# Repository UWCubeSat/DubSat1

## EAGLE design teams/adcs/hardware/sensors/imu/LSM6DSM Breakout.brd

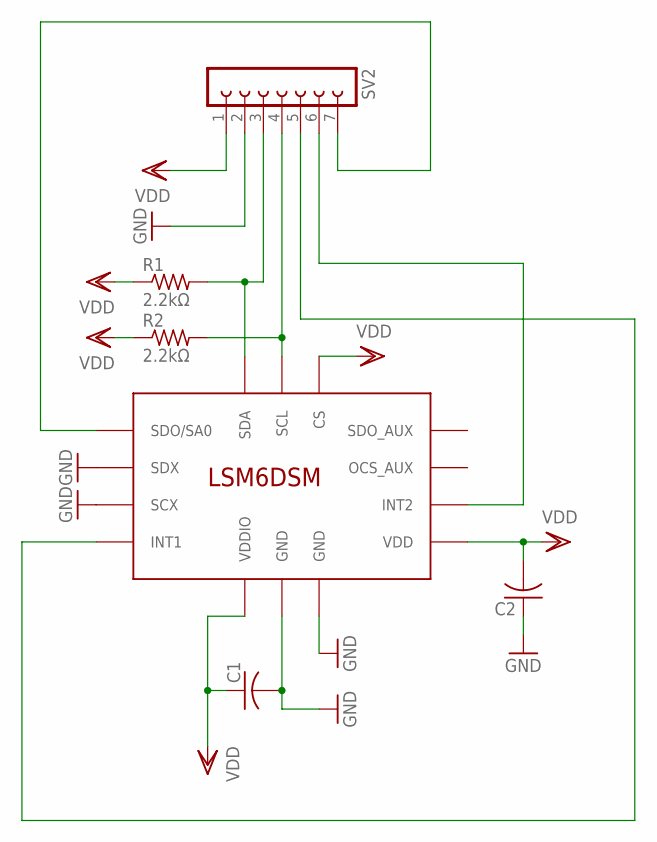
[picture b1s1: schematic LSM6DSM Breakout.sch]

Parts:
C1, C2: C-USC0805; C0805
R1, R2: 2.2kΩ; M0805
SV2: FE07-1; FE07
U$1: LSM6DSM

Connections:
GND: C1.2, C2.1, SV2.2, U$1.GND@1 (GND), U$1.GND@2 (GND), U$1.SCX, U$1.SDX
unnamed: SV2.5, U$1.INT1
unnamed: R1.2, SV2.3, U$1.SDA
unnamed: R2.2, SV2.4, U$1.SCL
unnamed: SV2.6, U$1.INT2
unnamed: SV2.7, U$1.SDO/SA0
VDD: C1.1, C2.2, R1.1, R2.1, SV2.1, U$1.CS, U$1.VDD, U$1.VDDIO

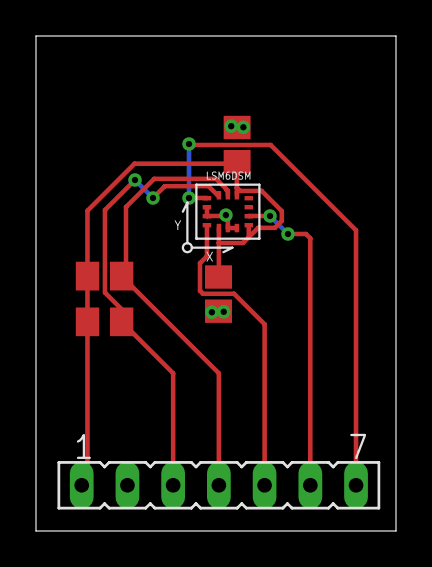
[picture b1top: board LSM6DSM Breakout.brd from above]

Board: 2 copper layers, 20.0 x 27.5 mm, 6 parts (0 on the bottom side), 7 nets.

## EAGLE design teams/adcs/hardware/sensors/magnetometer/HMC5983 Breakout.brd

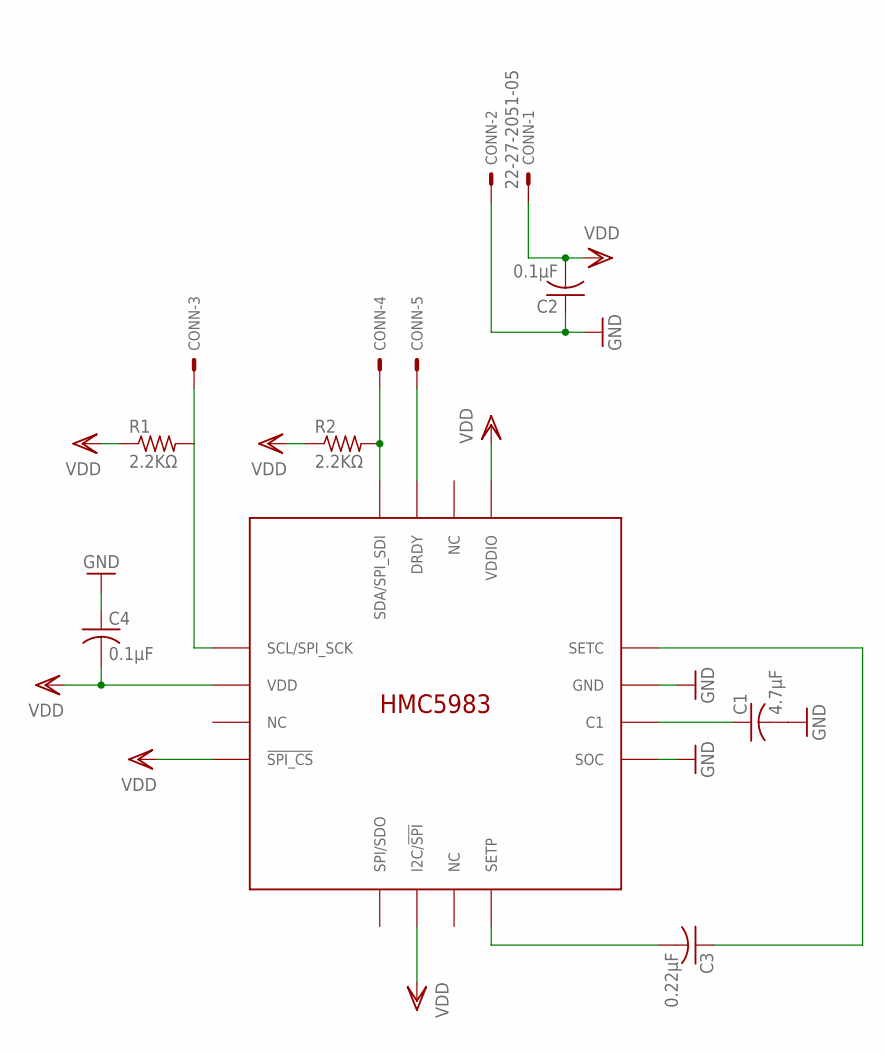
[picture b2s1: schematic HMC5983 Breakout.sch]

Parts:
C1: 4.7µF; C0805
C2: 0.1µF; C0805
C3: 0.22µF; C0805
C4: 0.1μF; C0805
CONN: 22-27-2051-05; 6410-05
R1, R2: 2.2KΩ; R0805
U$1: HMC5983

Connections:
GND: C1.2, C2.1, C4.1, CONN.2, U$1.GND, U$1.SOC
unnamed: CONN.4, R2.2, U$1.SDA/SPI_SDI
unnamed: CONN.3, R1.2, U$1.SCL/SPI_SCK
unnamed: CONN.5, U$1.DRDY
unnamed: C1.1, U$1.C1
unnamed: C3.2, U$1.SETP
unnamed: C3.1, U$1.SETC
VDD: C2.2, C4.2, CONN.1, R1.1, R2.1, U$1.!SPI_CS, U$1.I2C/!SPI, U$1.VDD, U$1.VDDIO

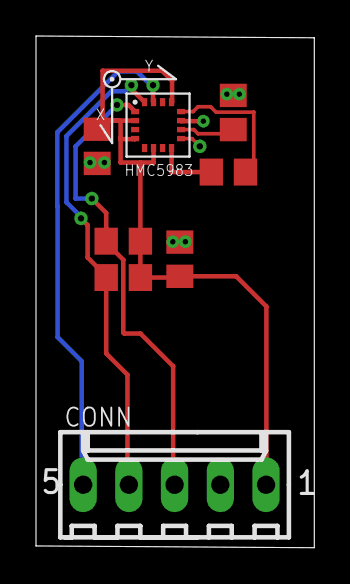
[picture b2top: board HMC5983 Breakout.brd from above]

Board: 2 copper layers, 15.5 x 28.4 mm, 8 parts (0 on the bottom side), 8 nets.

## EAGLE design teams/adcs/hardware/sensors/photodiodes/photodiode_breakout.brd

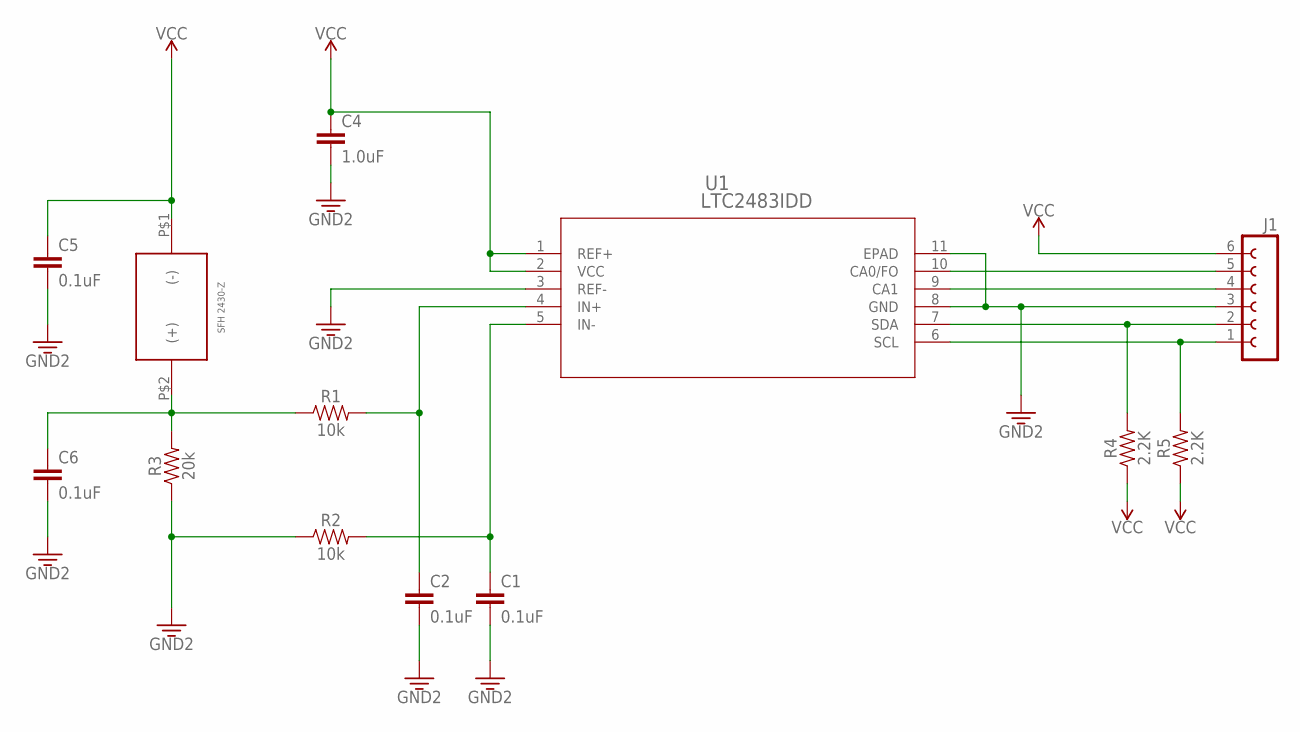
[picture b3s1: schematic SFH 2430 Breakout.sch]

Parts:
C1, C2, C5, C6: 0.1uF; 0603
C4: 1.0uF; 0805
J1: FE06-1; FE06
R1, R2: 10k; 0805
R3: 20k; 0805
R4, R5: 2.2K; 0805
U1: LTC2483IDD; DFN-10_DD
U$1: SFH-2430-Z; DIL

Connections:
GND: C1.2, C2.2, C4.2, C5.2, C6.2, J1.3, R2.1, R3.1, U1.3 (REF-), U1.8 (GND), U1.11 (EPAD)
unnamed: J1.1, R5.2, U1.6 (SCL)
unnamed: C1.1, R2.2, U1.5 (IN-)
unnamed: C2.1, R1.2, U1.4 (IN+)
unnamed: J1.2, R4.2, U1.7 (SDA)
unnamed: J1.4, U1.9 (CA1)
unnamed: J1.5, U1.10 (CA0/FO)
unnamed: C6.1, R1.1, R3.2, U$1.P$2 ((+))
VCC: C4.1, C5.1, J1.6, R4.1, R5.1, U1.1 (REF+), U1.2 (VCC), U$1.P$1 ((-))

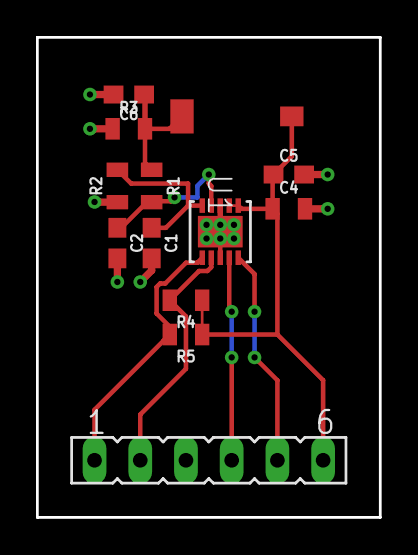
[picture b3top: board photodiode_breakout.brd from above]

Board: 2 copper layers, 19.1 x 26.7 mm, 13 parts (0 on the bottom side), 9 nets.

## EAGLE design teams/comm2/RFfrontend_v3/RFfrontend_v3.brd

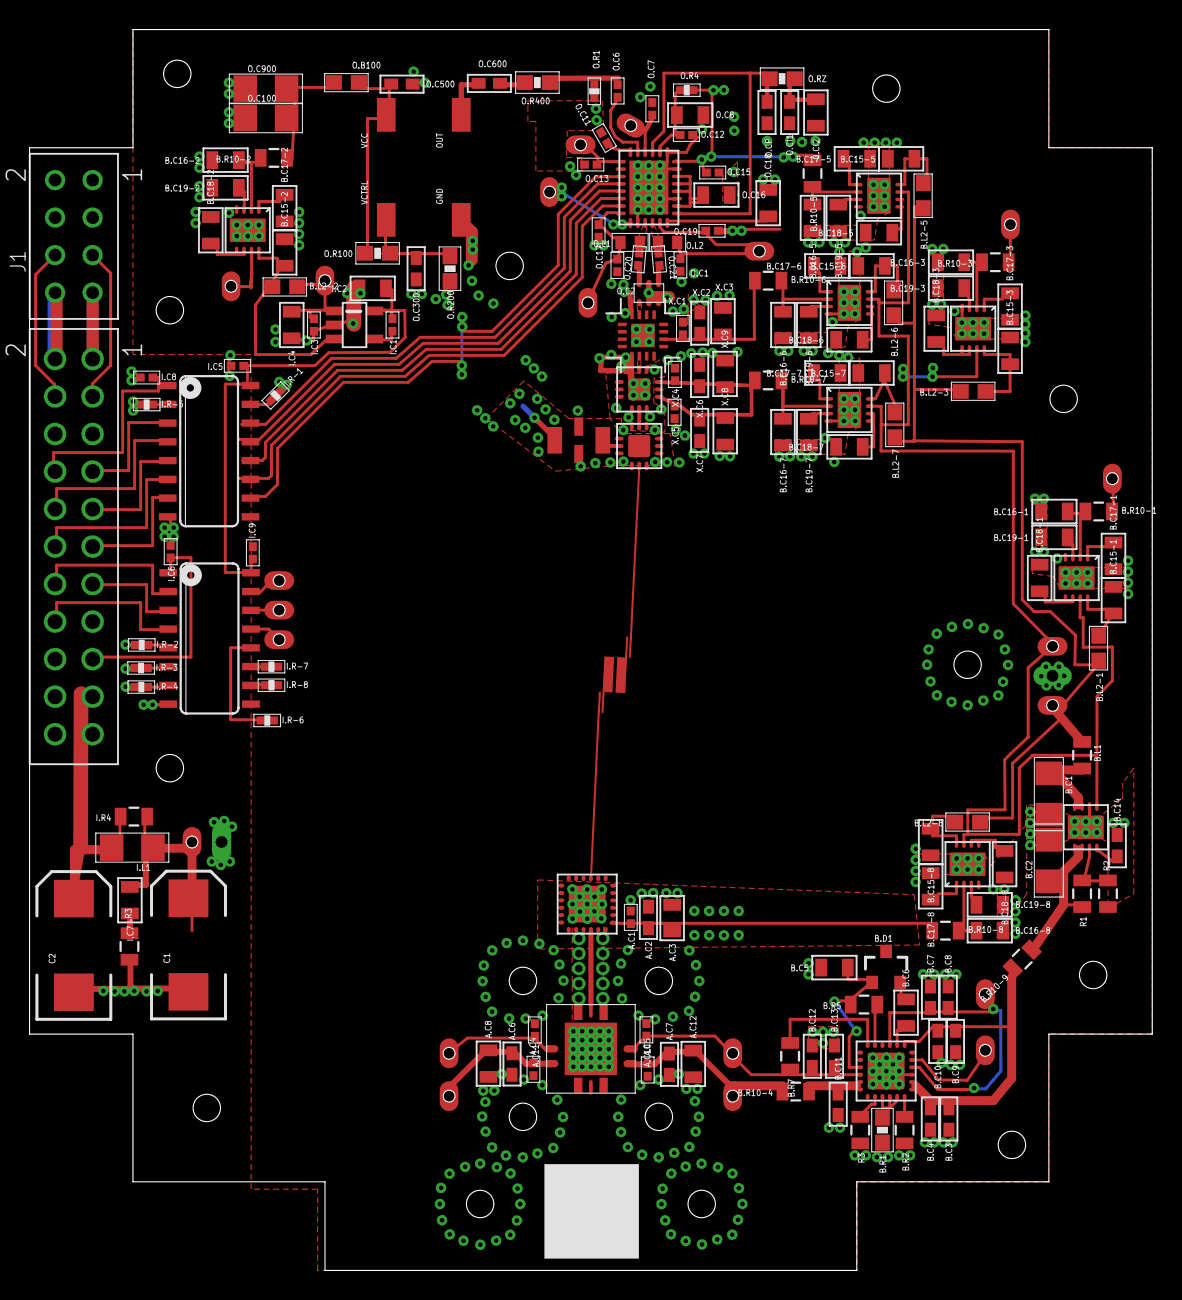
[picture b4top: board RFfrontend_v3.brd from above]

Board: 3 copper layers, 76.0 x 84.0 mm, 213 parts (1 on the bottom side), 117 nets.

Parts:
0.CI2: 0805
3.3V: 1PIN_B-T-B_TOPPAD
A.C1, A.C4, A.C5, A.C10, A.C11: 0402-CAP
A.C2, A.C6, A.C7: 0603-CAP
A.C3, A.C8, A.C12: 0805
B.C1, B.C2: 4.7u; 1206
B.C3, B.C8, B.C9, B.C12: 4.7u; 0603-CAP
B.C4, B.C7, B.C10, B.C11, B.C13, B.C14: 10n; 0603-CAP
B.C5, B.C15-1, B.C15-2, B.C15-3, B.C15-5, B.C15-6, B.C15-7, B.C15-8, B.C16-1, B.C16-2, B.C16-3, B.C16-5, B.C16-6, B.C16-7, B.C16-8, B.C17-1, B.C17-2, B.C17-3, B.C17-5, B.C17-6, B.C17-7, B.C17-8: 10u; 0805
B.C6, B.C18-1, B.C18-2, B.C18-3, B.C18-5, B.C18-6, B.C18-7, B.C18-8, B.C19-1, B.C19-2, B.C19-3, B.C19-5, B.C19-6, B.C19-7, B.C19-8: 1u; 0805
B.D1: ONSEMI_DIODE_BAT54SL; SOT23-3
B.L1, B.R10-1, B.R10-2, B.R10-3, B.R10-4, B.R10-5, B.R10-6, B.R10-7, B.R10-8, B.R10-9: 0805
B.L2-1, B.L2-2, B.L2-3, B.L2-5, B.L2-6, B.L2-7, B.L2-8: 0603
B.R1: 5k; 0603-RES
B.R2: 10k; 0805
B.R5, B.R7: 1.6M; 0805
C1, C2: EIA7343
I.C1, I.C3, I.C5, I.C6, I.C8, I.C9: .1u; 0402-CAP
I.C2, I.C4, I.C7: 1u; 0805
I.L1: 1206
I.R3, I.R4: 0805
I.R-1, I.R-2, I.R-3, I.R-4, I.R-5, I.R-6, I.R-7, I.R-8: 0402-RES
J1: SLW-104-01-X-D
O-3.3V: 1PIN_B-T-B_TOPPAD
O.B100: 0603
O.C1, O.C2, O.C6, O.C7, O.C11, O.C12, O.C13, O.C15, O.C17, O.C19, O.C20, O.C21: 0402-CAP
O.C8, O.C16, O.C18: 0805
O.C100, O.C900: 1206
O.C300, O.C500, O.C600, O.CI1, O.CP: 0603-CAP
O.L1, O.L2: C0402
O.R1, O.R4: 0402-RES
O.R100, O.R200, O.R400, O.RZ: 0603-RES
R1, R2: 0805
R3: 200; 0805
U$1: LINEAR_LTC6946; QFN_28PIN
U$9, U$18, U$19, U$20, U$25, U$26, U$28, U$35, U$36, U$153, U$154, U$155, U$157, U$174, U$175, U$176, U$177, U$189, U$190: 1PIN_B-T-B_TOPPAD
U$13: CRYSTEK_601964; 4_PIN_9X14MM
U$14: HITTITE_HMC369; LP3
U$15: MINICIRCUITS_LPF; FV1206
U$22: HITTITE_HMC576; 12PIN_QFN
U$29: HITTITE_HMC292; 12PIN_QFN
U$39: JOHNSON_5500BL15U0100; 6_PIN_BALUN
U$41: BPF_24GHZ
U$43: HITTITE_HMC383; 24-QFN
U$44: HITTITE_HMC5445; 16PIN_SMT
U$45, U$158, U$159, U$160, U$161, U$162, U$163, U$164, U$165, U$166, U$167, U$170, U$171, U$172, U$173, U$178: #1-72_BOLT_HOLE
U$51, U$111: ANALOG_ADUM162N0BRZ; SO16
U$61: ANALOG_LDO_ADM7172; 8-LFCSP
U$62: HITTITE_HMC980LP4E; 24-QFN
U$84, U$95, U$103, U$119, U$127, U$135, U$143: ANALOG_LDO_ADM7150; 8-LFCSP
U$113: LINEAR_LDO_LT1761-X; SOT-23-5
U$151: RF_FRONT_END_OUTLINE_V1
U$152, U$156: 1PIN_B-T-B_GROUND
U$169: TE_UMCC_CONNECTOR; 3_PIN_UMCC
U$180: SSW-111-XX-XXX-D
X.C1, X.C4, X.C5: 0402-CAP
X.C2, X.C6, X.C7: 0603-CAP
X.C3, X.C8, X.C9: 0805

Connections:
6.3V: B.C3.1, B.C4.1, B.C9.1, B.C10.1, B.R10-9.1, R1.2, U$62.P$1, U$62.P$2, U$62.P$7
12GHZ: U$14.PIN10, U$22.P2
A-4.8V: B.C7.1, B.C8.1, B.C16-1.1, B.R10-1.1, B.R10-1.2, U$26.P$1, U$28.P$1, U$62.P$4, U$62.P$9, U$84.P$2
A-5V: A.C1.2, A.C2.2, A.C3.2, B.R10-8.1, U$43.P$19
A-VDD: A.C4.2, A.C5.2, A.C6.2, A.C7.2, A.C8.2, A.C12.2, B.C11.2, B.R10-4.1, B.R10-4.2, U$44.P1, U$44.P11, U$62.P$17, U$62.P$18, U$174.P$1, U$175.P$1
A-VGG: A.C10.2, A.C11.2, B.C12.1, B.C13.1, B.R7.2, U$44.P2, U$44.P10, U$62.P$16, U$176.P$1, U$177.P$1
AGND: 0.CI2.1, A.C1.1, A.C2.1, A.C3.1, A.C4.1, A.C5.1, A.C6.1, A.C7.1, A.C8.1, A.C10.1, A.C11.1, A.C12.1, B.C1.2, B.C2.2, B.C3.2, B.C4.2, B.C5.2, B.C7.2, B.C8.2, B.C9.2, B.C10.2, B.C11.1, B.C12.2, B.C13.2, B.C14.2, B.C15-1.2, B.C15-2.2, B.C15-3.2, B.C15-5.2, B.C15-6.2, B.C15-7.2, B.C15-8.2, B.C16-1.2, B.C16-2.2, B.C16-3.2, B.C16-5.2, B.C16-6.2, B.C16-7.2, B.C16-8.2, B.C17-1.1, B.C17-2.1, B.C17-3.1, B.C17-5.1, B.C17-6.1, B.C17-7.1, B.C17-8.1, B.C18-1.2, B.C18-2.2, B.C18-3.2, B.C18-5.2, B.C18-6.2, B.C18-7.2, B.C18-8.2, B.C19-1.2, B.C19-2.2, B.C19-3.2, B.C19-5.2, B.C19-6.2, B.C19-7.2, B.C19-8.2, B.D1.3, B.R1.2, B.R2.2, C1.C, C2.C, I.C2.2, I.C3.2, I.C4.2, I.C5.2, I.C9.2, I.R3.1, I.R-1.2, I.R-6.2, I.R-7.2, I.R-8.2, O.C1.2, O.C2.2, O.C7.1, O.C8.2, O.C11.2, O.C12.2, O.C13.1, O.C15.2, O.C16.2, O.C17.2, O.C18.2, O.C19.1, O.C100.1, O.C300.2, O.C500.2, O.C900.1, O.CI1.1, O.CP.2, O.R1.2, O.R200.1, R2.1, R3.2, U$1.P$10, U$1.P$17, U$1.P$21, U$1.P$23, U$1.P$29, U$13.GND, U$14.PAD_GND, U$14.PIN4, U$14.PIN9, U$15.P$1, U$15.P$2, U$22.P1, U$22.P3, U$22.P7, U$22.P9, U$22.P$13, U$29.P1, U$29.P3, U$29.P4, U$29.P6, U$29.P7, U$29.P9, U$29.P$13, U$39.P$2, U$39.P$3, U$39.P$5, U$43.P$14, U$43.P$15, U$43.P$17, U$43.P$18, U$43.P$25, U$44.GNDP, U$44.P5, U$44.P7, U$44.P13, U$44.P15, U$51.9, U$61.P$6, U$61.P$9, U$62.P$3, U$62.P$25, U$84.P$4, U$84.P$9, U$95.P$4, U$95.P$9, U$103.P$4, U$103.P$9, U$111.9, U$113.P$2, U$119.P$4, U$119.P$9, U$127.P$4, U$127.P$9, U$135.P$4, U$135.P$9, U$143.P$4, U$143.P$9, U$152.P$2, U$156.P$2, U$169.P$2, U$169.P$3, U$180.20, U$180.22, X.C1.1, X.C2.1, X.C3.1, X.C4.1, X.C5.2, X.C6.1, X.C7.2, X.C8.1, X.C9.2
CS: U$1.P$4, U$111.14
ISO-3.3V: I.C1.1, I.C2.1, I.C5.1, I.C9.1, U$51.16, U$111.16, U$113.P$5
ISO-BOT-VCC: I.C6.2, U$51.1, U$180.17
ISO-TOP-VCC: I.C8.2, U$111.1, U$180.8
LDO-EN: U$35.P$1, U$36.P$1, U$51.15, U$61.P$5, U$84.P$7, U$95.P$7, U$103.P$7, U$119.P$7, U$127.P$7, U$135.P$7, U$143.P$7, U$153.P$1
MCU-CS: U$111.3, U$180.7
MCU-GND: I.C6.1, I.C8.1, I.R-2.1, I.R-3.1, I.R-4.1, I.R-5.1, U$51.8, U$111.8, U$180.18
MCU-LDO-EN: U$51.2, U$180.14
MCU-MUTE: U$51.4, U$180.16
MCU-PA-EN: U$51.3, U$180.13
MCU-SCLK: U$111.4, U$180.10
MCU-SDI: U$111.5, U$180.9
MCU-SDO: U$111.6, U$180.12
MCU-STAT: U$111.7, U$180.11
MUTE: U$1.P$9, U$51.13, U$189.P$1, U$190.P$1
unnamed: O.C8.1, O.C12.1, O.R4.1, U$1.P$24
unnamed: O.C16.1, U$1.P$16, U$1.P$18, U$1.P$19, U$1.P$20
unnamed: O.C20.2, U$39.P$6
unnamed: 0.CI2.2, O.CI1.2, O.RZ.1
unnamed: O.CP.1, O.RZ.2, U$1.P$15, U$1.P$25
unnamed: O.C18.1, U$1.P$14
unnamed: O.C20.1, O.L1.2, U$1.P$11
unnamed: O.C21.1, O.L2.1, U$1.P$12
unnamed: O.C21.2, U$39.P$4
unnamed: U$14.PIN3, U$39.P$1
unnamed: O.C11.1, U$1.P$28
unnamed: O.C6.2, U$1.P$27
unnamed: O.C6.1, O.R1.1, O.R400.1
unnamed: O.B100.2, O.C500.1, O.R100.2, U$13.VCC
unnamed: O.C300.1, O.R100.1, O.R200.2, U$13.VCTRL
unnamed: O.C600.1, U$13.OUT
unnamed: U$22.P8, U$29.P2
unnamed: O.C600.2, O.R400.2
unnamed: U$15.P$4, U$29.P5
unnamed: U$29.P8, U$41.IN
unnamed: U$41.OUT, U$43.P$3
unnamed: U$43.P$16, U$44.P6
unnamed: R1.1, R2.2, U$61.P$3
unnamed: I.R-1.1, U$111.15
unnamed: U$15.P$3, U$169.P$1
unnamed: R3.1, U$62.P$20
unnamed: B.R7.1, U$62.P$12
unnamed: B.C5.1, B.D1.1, B.R5.2, U$62.P$15
unnamed: B.R5.1, U$62.P$11
unnamed: B.C6.1, U$62.P$8
unnamed: B.C6.2, B.D1.2
unnamed: B.R1.1, U$62.P$21, U$62.P$22, U$62.P$23
unnamed: B.R2.1, U$62.P$24
unnamed: B.C14.1, U$61.P$4
unnamed: B.C15-1.1, B.L2-1.1, U$84.P$8
unnamed: B.C17-1.2, U$84.P$1
unnamed: B.C18-1.1, U$84.P$5, U$84.P$6
unnamed: B.C15-2.1, B.L2-2.1, U$95.P$8
unnamed: J1.7, U$180.1
unnamed: B.C19-1.1, U$84.P$3
unnamed: B.C18-2.1, U$95.P$5, U$95.P$6
unnamed: B.C19-2.1, U$95.P$3
unnamed: B.C16-2.1, B.R10-2.2, U$95.P$2
unnamed: B.C15-5.1, B.L2-5.1, U$119.P$8
unnamed: B.C15-3.1, B.L2-3.1, U$103.P$8
unnamed: B.C17-3.2, U$103.P$1
unnamed: B.C18-3.1, U$103.P$5, U$103.P$6
unnamed: B.C19-3.1, U$103.P$3
unnamed: B.C16-3.1, B.R10-3.2, U$103.P$2
unnamed: B.C17-5.2, U$119.P$1
unnamed: I.C1.2, U$113.P$4
unnamed: J1.5, U$180.3
unnamed: B.C17-2.2, U$95.P$1
unnamed: B.C18-5.1, U$119.P$5, U$119.P$6
unnamed: B.C19-5.1, U$119.P$3
unnamed: B.C16-5.1, B.R10-5.2, U$119.P$2
unnamed: B.C15-6.1, B.L2-6.1, U$127.P$8
unnamed: B.C17-6.2, U$127.P$1
unnamed: B.C18-6.1, U$127.P$5, U$127.P$6
unnamed: I.R-5.2, U$111.2
unnamed: B.C16-6.1, B.R10-6.2, U$127.P$2
unnamed: B.C15-7.1, B.L2-7.1, U$135.P$8
unnamed: B.C17-7.2, U$135.P$1
unnamed: B.C18-7.1, U$135.P$5, U$135.P$6
unnamed: B.C19-7.1, U$135.P$3
unnamed: B.C16-7.1, B.R10-7.2, U$135.P$2
unnamed: B.C15-8.1, B.L2-8.1, U$143.P$8
unnamed: B.C17-8.2, U$143.P$1
unnamed: B.C18-8.1, U$143.P$5, U$143.P$6
unnamed: B.C19-8.1, U$143.P$3
unnamed: B.C16-8.1, B.R10-8.2, U$143.P$2
unnamed: B.C2.1, B.R10-9.2, U$61.P$1, U$61.P$2
unnamed: I.C7.2, I.R3.2
unnamed: J1.8, U$180.2
unnamed: J1.6, U$180.4
unnamed: I.R-2.2, U$51.5
unnamed: I.R-4.2, U$51.7
unnamed: I.R-3.2, U$51.6
unnamed: I.R-6.1, U$51.12
unnamed: I.R-7.1, U$51.11
unnamed: I.R-8.1, U$51.10
unnamed: B.C19-6.1, U$127.P$3
O-3.3V: 3.3V.P$1, B.R10-3.1, O-3.3V.P$1, O.C1.1, O.C2.1, O.C7.2, O.C13.2, O.C17.1, O.C19.2, O.L1.1, O.L2.2, U$1.P$1, U$1.P$8, U$1.P$13, U$1.P$26, U$9.P$1, U$18.P$1, U$19.P$1
O-5V: B.R10-5.1, O.C15.1, O.R4.2, U$1.P$22
PA-EN: U$51.14, U$62.P$5, U$154.P$1, U$157.P$1
REF-3.3V: B.R10-2.1, O.B100.1, O.C100.2, O.C900.2
SCLK: U$1.P$5, U$111.13
SDI: U$1.P$6, U$111.12
SDO: U$1.P$7, U$111.11
STAT: U$1.P$3, U$111.10
VBAT: B.L1.1, B.L2-1.2, B.L2-2.2, B.L2-3.2, B.L2-5.2, B.L2-6.2, B.L2-7.2, B.L2-8.2, C2.A, I.C3.1, I.C4.1, I.C7.1, I.L1.2, I.R4.1, U$20.P$1, U$25.P$1, U$113.P$1, U$113.P$3, U$155.P$1
VBAT_DIRTY: C1.A, I.L1.1, I.R4.2, U$180.19, U$180.21
VIN: B.C1.1, B.L1.2, U$61.P$7, U$61.P$8
X1-5V: B.R10-6.1, U$14.PIN14, X.C1.2, X.C2.2, X.C3.2
X2-5V: B.R10-7.1, U$22.P10, U$22.P12, X.C4.2, X.C5.1, X.C6.2, X.C7.1, X.C8.2, X.C9.1

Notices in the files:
parts and their libraries:
SparkFun-Capacitors: Licensing: Creative Commons ShareAlike 4.0 International - https://creativecommons.org/licenses/by-sa/4.0
